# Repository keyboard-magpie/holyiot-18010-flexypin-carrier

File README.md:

# holyiot-18010-flexypin-carrier
A board making use of solderparty's wonderful flexypins (https://github.com/solderparty/flexypin) to enable easy flashing of the holyiot 18010 module

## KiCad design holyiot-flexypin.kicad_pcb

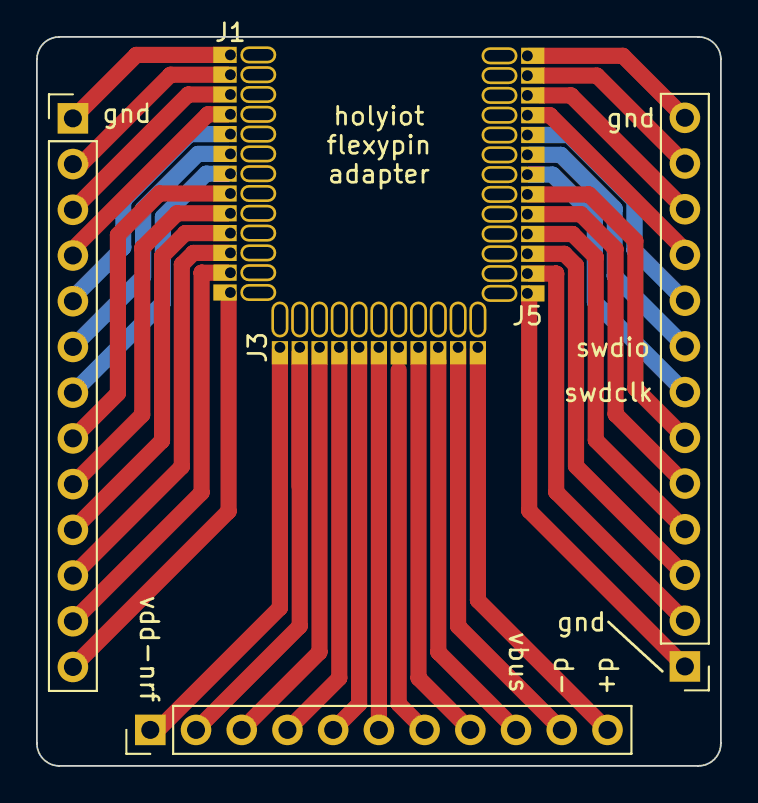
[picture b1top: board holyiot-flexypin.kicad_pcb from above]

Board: 2 copper layers, 38.0 x 40.5 mm, 6 parts (0 on the bottom side), 37 nets.

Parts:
 : Conn_01x13_Male; PinHeader_1x13_P2.54mm_Vertical
J1, J5: Conn_01x13_Male; FlexyPin_1x13_P1.10mm
J3: Conn_01x11_Male; FlexyPin_1x11_P1.10mm
J4: Conn_01x11_Male; PinHeader_1x11_P2.54mm_Vertical
J6: Conn_01x13_Male; PinHeader_1x13_P2.54mm_Vertical

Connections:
unnamed: .1, J1.1
unnamed: .2, J1.2
unnamed: .3, J1.3
unnamed: .4, J1.4
unnamed: .5, J1.5
unnamed: .6, J1.6
unnamed: .7, J1.7
unnamed: .8, J1.8
unnamed: .9, J1.9
unnamed: .10, J1.10
unnamed: .11, J1.11
unnamed: .12, J1.12
unnamed: .13, J1.13
unnamed: J3.1, J4.1
unnamed: J3.2, J4.2
unnamed: J3.3, J4.3
unnamed: J3.4, J4.4
unnamed: J3.5, J4.5
unnamed: J3.6, J4.6
unnamed: J3.7, J4.7
unnamed: J3.8, J4.8
unnamed: J3.9, J4.9
unnamed: J3.10, J4.10
unnamed: J3.11, J4.11
unnamed: J5.1, J6.1
unnamed: J5.2, J6.2
unnamed: J5.3, J6.3
unnamed: J5.4, J6.4
unnamed: J5.5, J6.5
unnamed: J5.6, J6.6
unnamed: J5.7, J6.7
unnamed: J5.8, J6.8
unnamed: J5.9, J6.9
unnamed: J5.10, J6.10
unnamed: J5.11, J6.11
unnamed: J5.12, J6.12
unnamed: J5.13, J6.13

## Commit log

2022-07-01 Create license
